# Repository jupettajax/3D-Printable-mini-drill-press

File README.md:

This is a precision drill press designed for mainly PCB drilling, it can be also used for other materials. Most parts can be 3D printed or purchased from regular hardware stores.

Electronic side consists of custom made microcontroller-controlled interface, that handles PID-tuning of the motor speed to maintain a stable drilling speed as well as setting desired drilling speeds.
BLDC-motor, -controller and the 7-segment display can be bought ready-made from Aliexpress, Links will be updated later.

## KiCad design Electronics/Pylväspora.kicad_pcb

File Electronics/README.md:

This is the electrical side of the Project

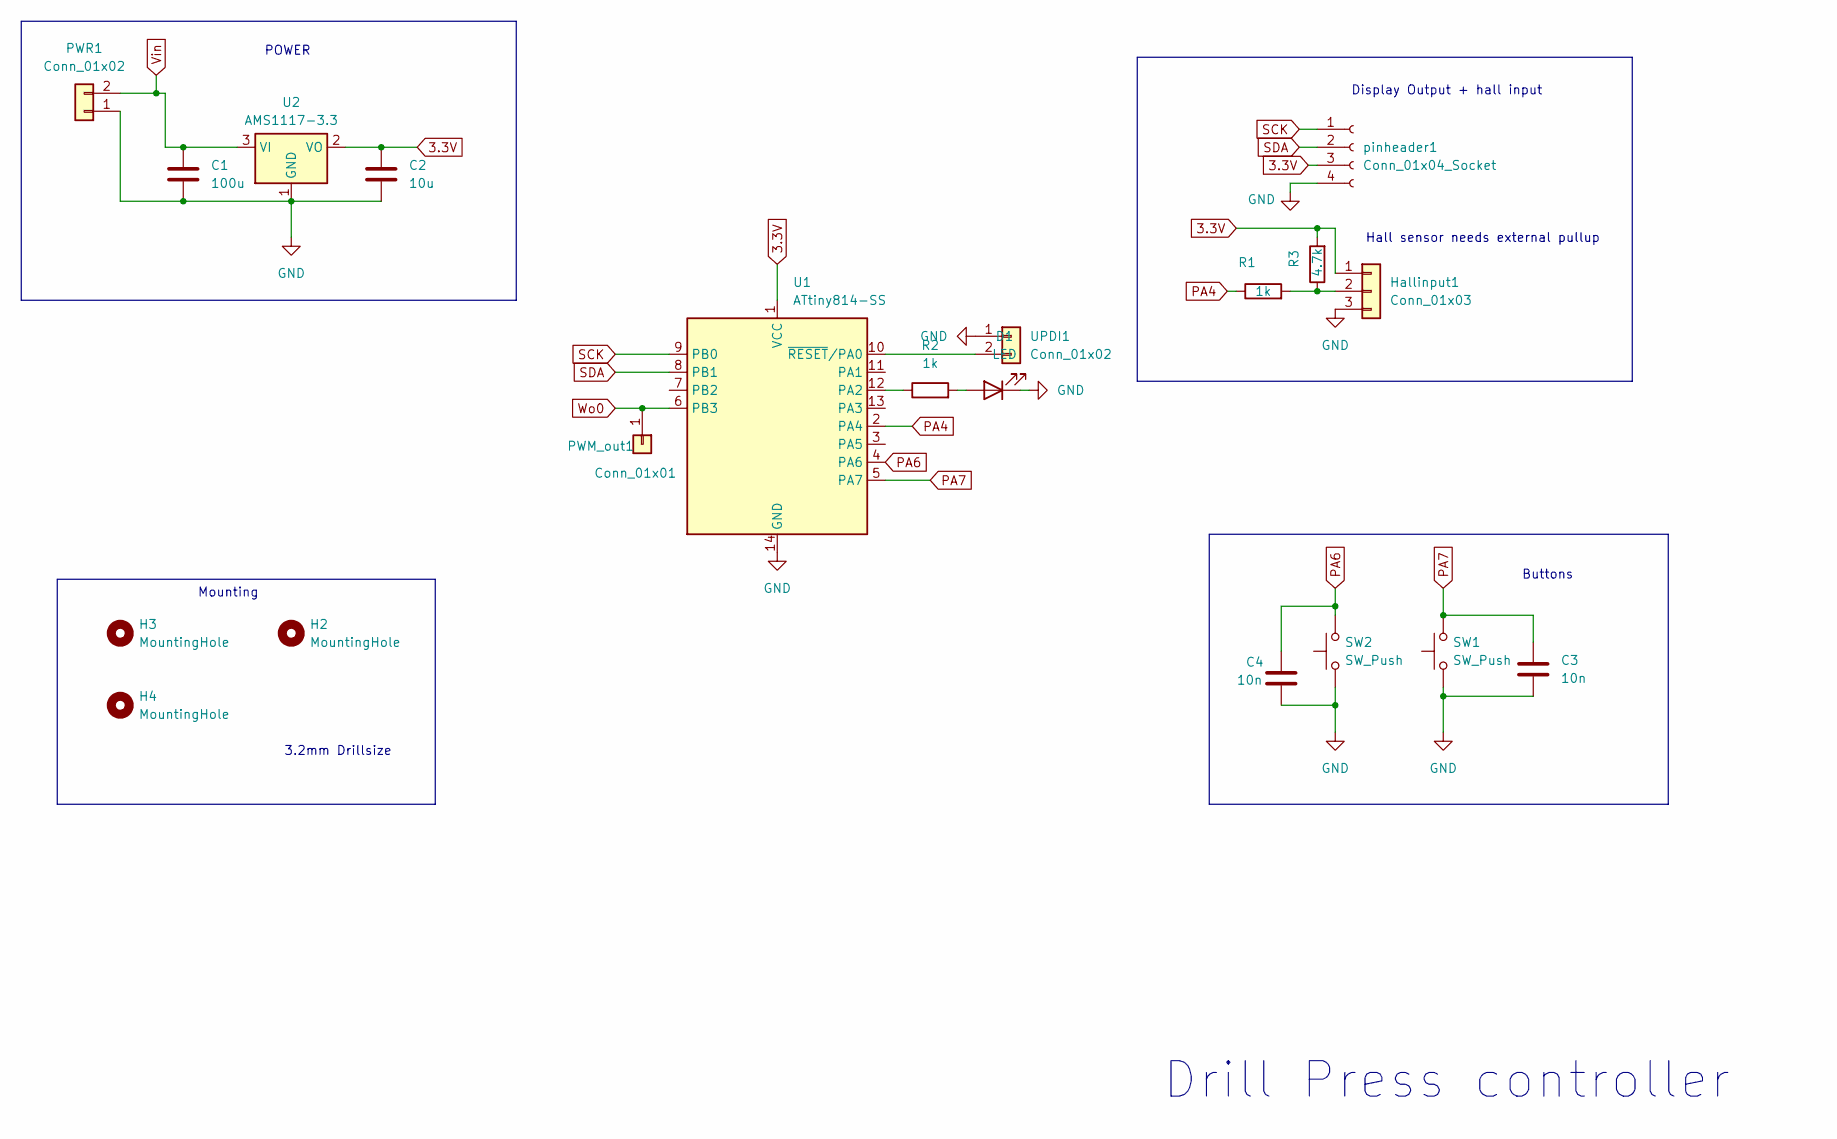
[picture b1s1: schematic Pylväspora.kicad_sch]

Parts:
C1: 100u; CP_Radial_D10.0mm_P5.00mm
C2: 10u; C_0603_1608Metric_Pad1.08x0.95mm_HandSolder
C3, C4: 10n; C_0603_1608Metric_Pad1.08x0.95mm_HandSolder
D1: LED; C_0603_1608Metric_Pad1.08x0.95mm_HandSolder
H2, H3, H4: MountingHole; MountingHole_3.2mm_M3
Hallinput1: Conn_01x03; JST_EH_B3B-EH-A_1x03_P2.50mm_Vertical
PWM_out1: Conn_01x01; PinHeader_1x01_P2.54mm_Vertical
PWR1: Conn_01x02; JST_EH_B2B-EH-A_1x02_P2.50mm_Vertical
R1, R2: 1k; R_1206_3216Metric_Pad1.30x1.75mm_HandSolder
R3: 4.7k; R_1206_3216Metric_Pad1.30x1.75mm_HandSolder
SW1, SW2: SW_Push; SW_PUSH_1P1T_6x3.5mm_H5.0_APEM_MJTP1250
U1: ATtiny814-SS; SOIC-14_3.9x8.7mm_P1.27mm
U2: AMS1117-3.3; SOT-223-3_TabPin2
UPDI1: Conn_01x02; PinSocket_1x02_P2.54mm_Vertical
pinheader1: Conn_01x04_Socket; PinSocket_1x04_P2.54mm_Vertical

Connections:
3.3V: C2.1, Hallinput1.1, R3.2, U1.1 (VCC), U2.2 (VO), pinheader1.3
GND: C1.2, C2.2, C3.2, C4.2, D1.1 (K), Hallinput1.3, PWR1.1, SW1.1, SW2.1, U1.14 (GND), U2.1 (GND), UPDI1.1, pinheader1.4
unnamed: D1.2 (A), R2.2
unnamed: Hallinput1.2, R1.2, R3.1
unnamed: R2.1, U1.12 (PA2)
unnamed: U1.10 (~RESET/PA0), UPDI1.2
PA4: R1.1, U1.2 (PA4)
PA6: C4.1, SW2.2, U1.4 (PA6)
PA7: C3.1, SW1.2, U1.5 (PA7)
SCK: U1.9 (PB0), pinheader1.1
SDA: U1.8 (PB1), pinheader1.2
Vin: C1.1, PWR1.2, U2.3 (VI)
Wo0: PWM_out1.1, U1.6 (PB3)

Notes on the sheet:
Mounting
Drill Press controller
Hall sensor needs external pullup
Buttons
POWER
3.2mm Drillsize
Display Output + hall input

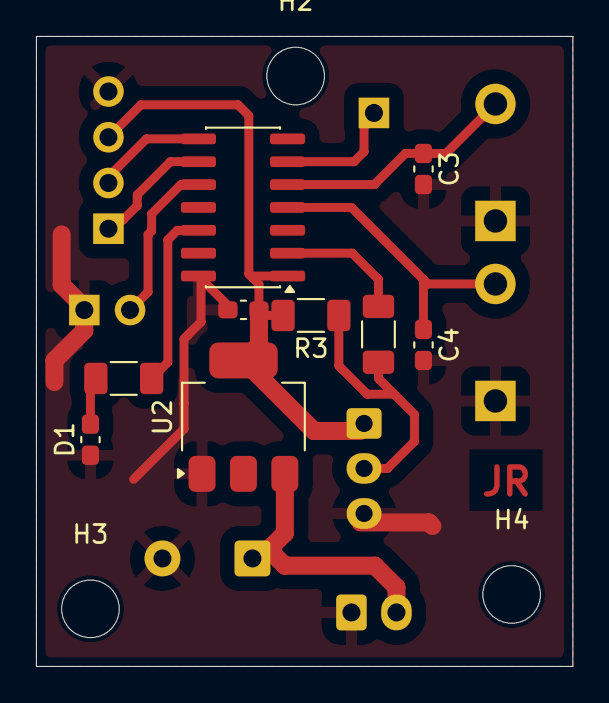
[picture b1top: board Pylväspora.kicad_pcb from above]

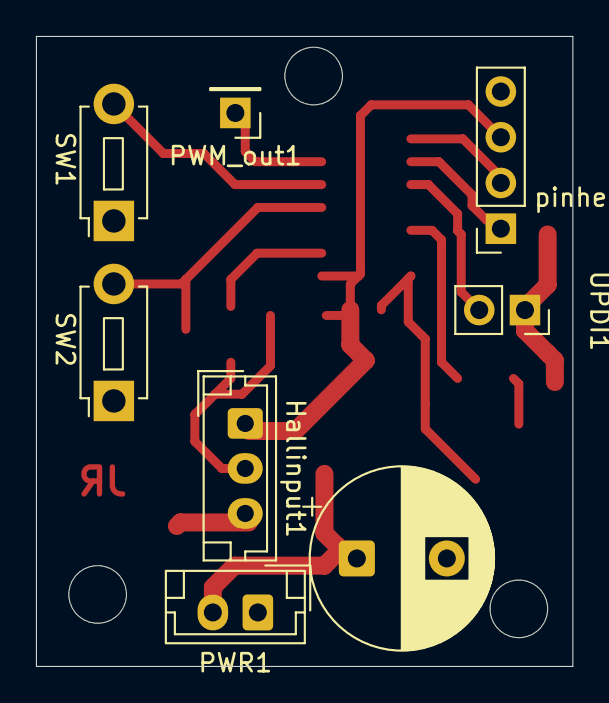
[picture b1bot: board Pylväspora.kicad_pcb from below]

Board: 2 copper layers, 29.8 x 35.0 mm, 20 parts (8 on the bottom side), 13 nets.

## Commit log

2026-01-03 Added KiCad Files
2026-01-03 Fixed location of KiCad files
2026-01-03 Corrected jst model footprints
2026-01-09 Software ios, display driving logic, buttons
    Software ios, display driving logic, buttons
2026-01-13 Added Motor hall sensor input and rpm calculations,, fixed logic
2026-01-14 Small schematic and layout fix
    Forgot a pullup resistor from hall input, added 4.7k pullup. Fixed incorrect measurement of RPM and increased update frequency in software
